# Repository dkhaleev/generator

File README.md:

# generator
arduino-based DDS generator

## Credits:

Implementation [[dimax](http://arduino.ru/forum/proekty/generator-s-reguliruemoei-chastotoi-na-arduino)]

LCD_5110 library [[http://www.rinkydinkelectronics](http://www.rinkydinkelectronics.com/library.php?id=45)]

LCD_5110 adaptation [[SSVS111](https://github.com/ssvs111/ARDUINO-LCD-NOKIA5110-SSVS-RUS)]

AVR DDS approach [[scienceprog](https://scienceprog.com/avr-dds-signal-generator-v20/)]

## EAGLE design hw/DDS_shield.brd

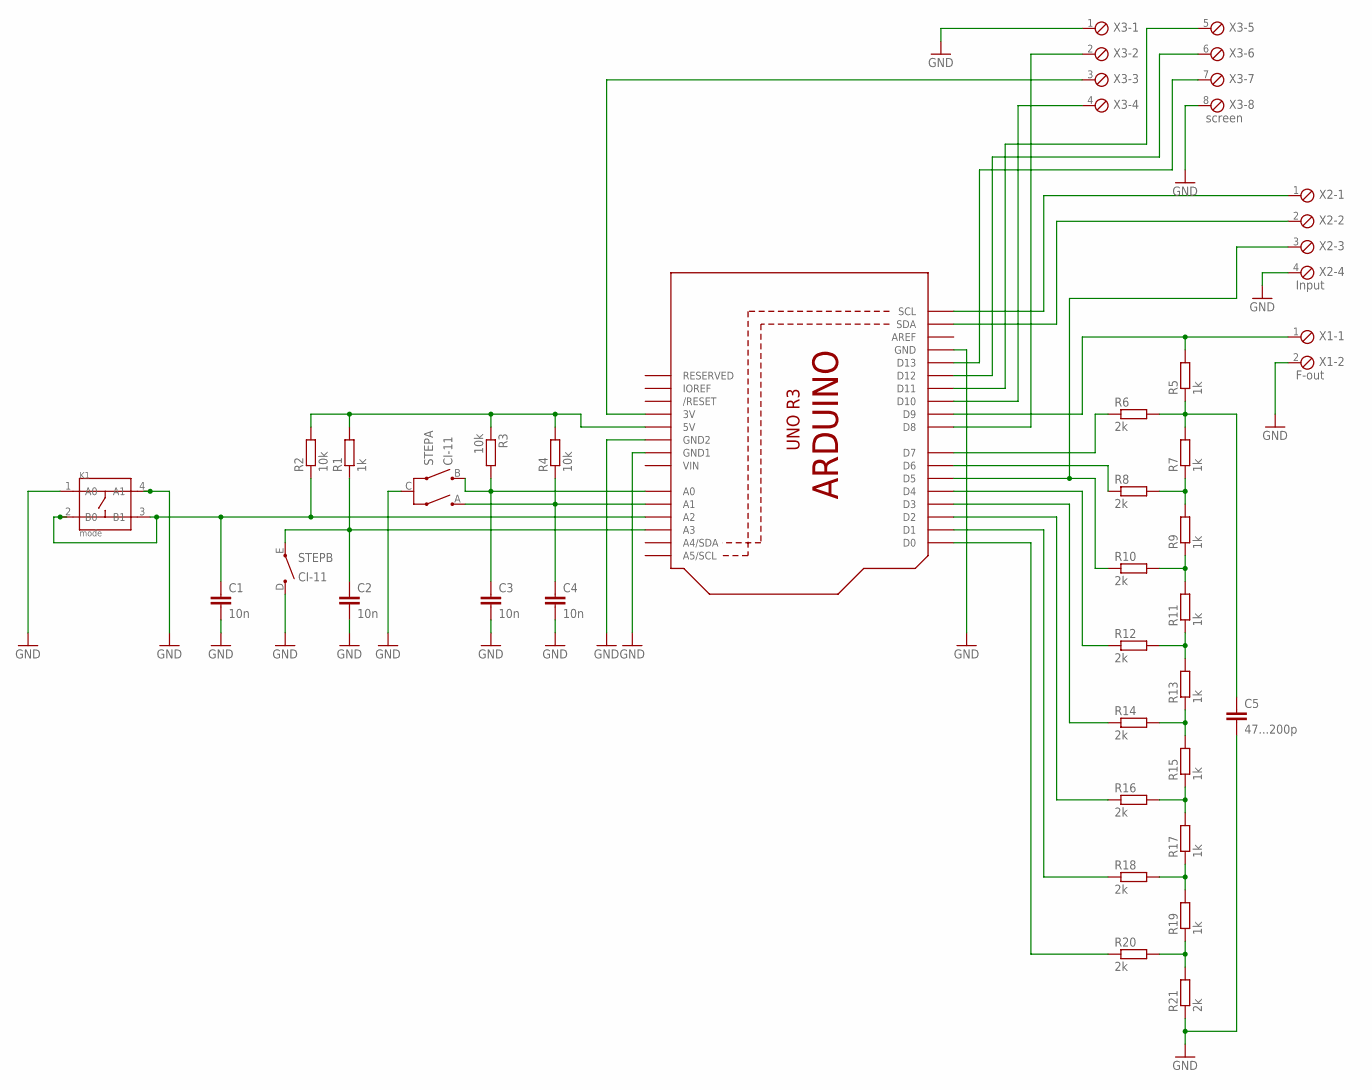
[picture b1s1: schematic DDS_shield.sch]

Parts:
C1, C2, C3, C4: 10n; C0805
C5: 47...200p; C0805
K1: mode; SW4-6.0X6.0X5.0MM
R1, R5, R7, R9, R11, R13, R15, R17, R19: 1k; M0805
R2, R3, R4: 10k; M0805
R6, R8, R10, R12, R14, R16, R18, R20, R21: 2k; M0805
STEP: CI-11
U1: ARDUINOR3-BPLACE
X1: F-out; 2POL254
X2: Input; 4POL254
X3: screen; 8POL254

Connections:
GND: C1.2, C2.2, C3.2, C4.2, C5.2, K1.1 (A0), K1.4 (A1), R21.1, STEP.C, STEP.D, U1.GND, U1.GND1, U1.GND2, X1.2, X2.4, X3.1, X3.8
unnamed: C1.1, K1.2 (B0), K1.3 (B1), R2.1, U1.A2
unnamed: C2.1, R1.1, STEP.E, U1.A3
unnamed: R1.2, R2.2, R3.1, R4.2, U1.5V
unnamed: C4.1, R4.1, STEP.A, U1.A1
unnamed: C3.1, R3.2, STEP.B, U1.A0
unnamed: R5.2, U1.D9, X1.1
unnamed: C5.1, R5.1, R6.2, R7.2
unnamed: R6.1, U1.D7
unnamed: R8.1, U1.D6
unnamed: R10.1, U1.D5, X2.3
unnamed: R12.1, U1.D4
unnamed: R20.1, U1.D0
unnamed: R18.1, U1.D1
unnamed: R7.1, R8.2, R9.2
unnamed: R14.1, U1.D3
unnamed: R16.1, U1.D2
unnamed: R9.1, R10.2, R11.2
unnamed: R11.1, R12.2, R13.2
unnamed: R13.1, R14.2, R15.2
unnamed: R15.1, R16.2, R17.2
unnamed: R17.1, R18.2, R19.2
unnamed: R19.1, R20.2, R21.2
unnamed: U1.D8, X3.2
unnamed: U1.SDA, X2.2
unnamed: U1.SCL, X2.1
unnamed: U1.3V, X3.3
unnamed: U1.D10, X3.4
unnamed: U1.D11, X3.5
unnamed: U1.D12, X3.6
unnamed: U1.D13, X3.7
VIN: U1.VIN

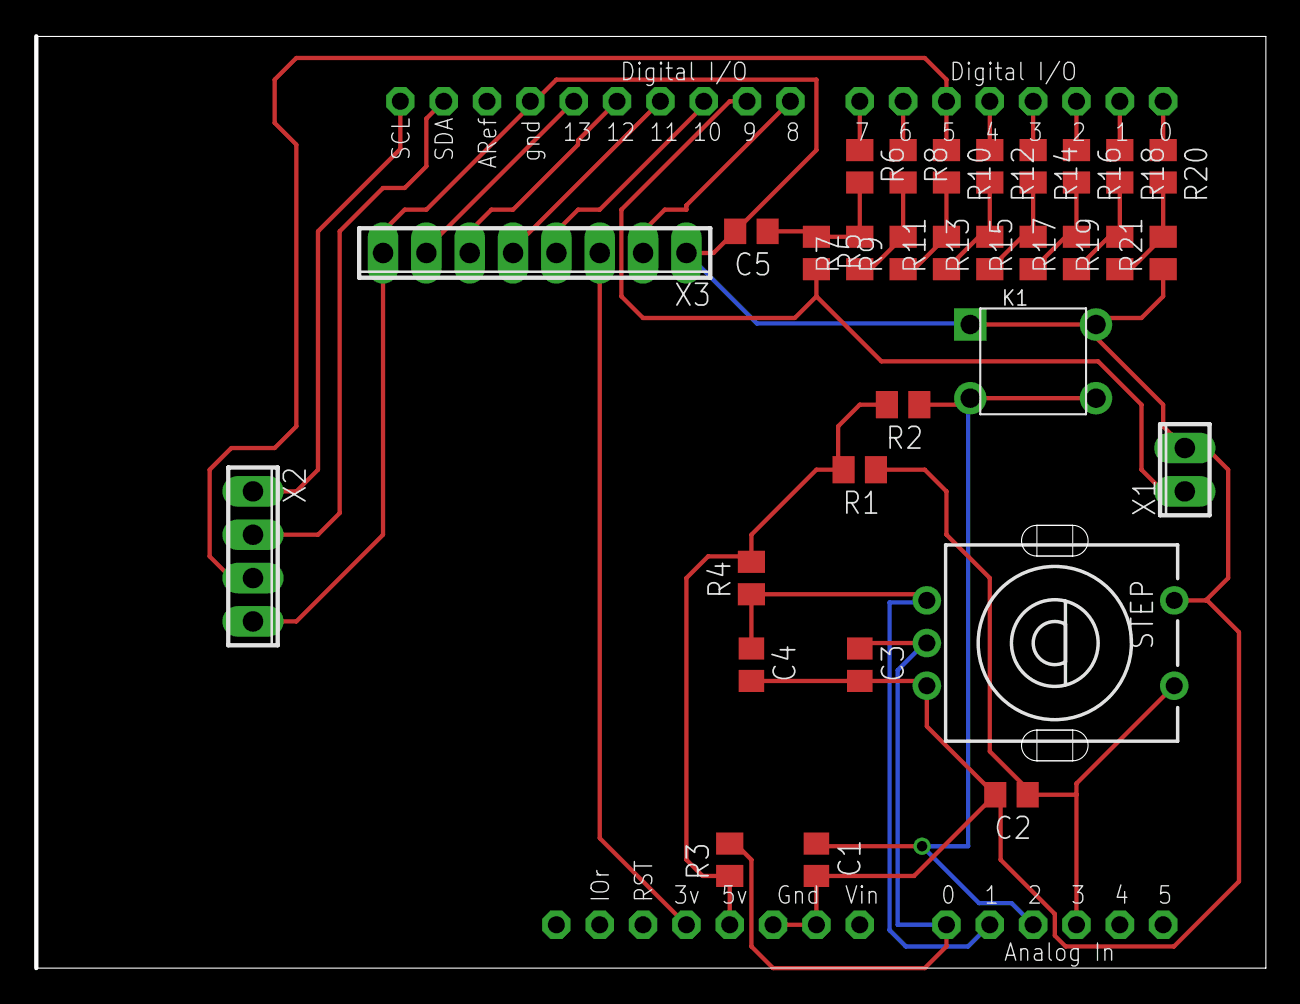
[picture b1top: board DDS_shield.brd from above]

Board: 2 copper layers, 71.9 x 54.6 mm, 32 parts (0 on the bottom side), 31 nets.

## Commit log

2018-01-03 added 5110 lib
2018-01-03 LCD test
2018-01-11 added schield schema
2018-01-11 arduino shield schematics for eagle CAD
2018-01-11 firmware sketch
2018-01-11 fix for readme misprint
2018-01-11 added extra ground terminals
2018-01-11 autorouted board for Eagle CAD
2018-01-14 updated extra GNDs on schema
2018-01-14 final board
2018-01-14 added board layout export
2018-01-14 mirrored template for toner transfer pcb
2018-01-14 added vectorized layers for top, bottom and drill layers
